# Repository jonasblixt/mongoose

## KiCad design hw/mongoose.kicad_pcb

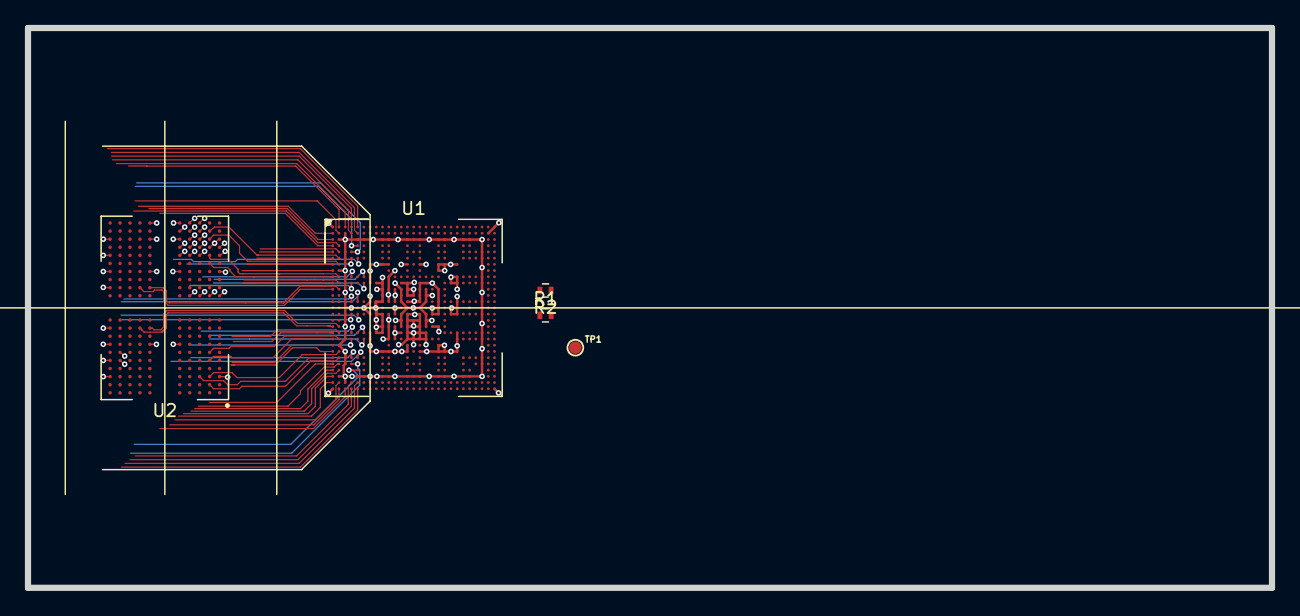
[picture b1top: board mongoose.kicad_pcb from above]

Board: 6 copper layers, 100.0 x 45.0 mm, 5 parts (0 on the bottom side), 80 nets.

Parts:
R1: R0402_240R; R0402
R2: R0402_10k; R0402
TP1: TP; TP_1mm
U1: MIMX8MM6DVTLZAA; BGA-486_27x27_P0.5mm_14.0x14.0mm
U2: MT53B256M32D1NP; BGA-200_12x22_10.0x14.5mm

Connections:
/IMX8MM/DRAM_CA0_A: U1.J6, U2.R2
/IMX8MM/DRAM_CA0_B: U1.W6, U2.H2
/IMX8MM/DRAM_CA1_A: U1.K6, U2.P2
/IMX8MM/DRAM_CA1_B: U1.V6, U2.J2
/IMX8MM/DRAM_CA2_A: U1.E4, U2.R9
/IMX8MM/DRAM_CA2_B: U1.AC4, U2.H9
/IMX8MM/DRAM_CA3_A: U1.D5, U2.R10
/IMX8MM/DRAM_CA3_B: U1.AD5, U2.H10
/IMX8MM/DRAM_CA4_A: U1.N4, U2.R11
/IMX8MM/DRAM_CA4_B: U1.R4, U2.H11
/IMX8MM/DRAM_CA5_A: U1.N5, U2.P11
/IMX8MM/DRAM_CA5_B: U1.R5, U2.J11
/IMX8MM/DRAM_CKE0_A: U1.F4, U2.P4
/IMX8MM/DRAM_CKE0_B: U1.AB4, U2.J4
/IMX8MM/DRAM_CKE1_A: U1.F5, U2.P5
/IMX8MM/DRAM_CKE1_B: U1.AB5, U2.J5
/IMX8MM/DRAM_CK_C_A: U1.L1, U2.P9
/IMX8MM/DRAM_CK_C_B: U1.U1, U2.J9
/IMX8MM/DRAM_CK_T_A: U1.L2, U2.P8
/IMX8MM/DRAM_CK_T_B: U1.U2, U2.J8
/IMX8MM/DRAM_CS0_N_A: U1.K4, U2.R4
/IMX8MM/DRAM_CS0_N_B: U1.W4, U2.H4
/IMX8MM/DRAM_CS1_N_A: U1.J4, U2.R3
/IMX8MM/DRAM_CS1_N_B: U1.V4, U2.H3
/IMX8MM/DRAM_DM0: U1.A4, U2.Y10
/IMX8MM/DRAM_DM1: U1.F1, U2.Y3
/IMX8MM/DRAM_DM2: U1.AB1, U2.C3
/IMX8MM/DRAM_DM3: U1.AG4, U2.C10
/IMX8MM/DRAM_DQ0: U1.A5, U2.AA11
/IMX8MM/DRAM_DQ1: U1.B5, U2.Y11
/IMX8MM/DRAM_DQ2: U1.D2, U2.V11
/IMX8MM/DRAM_DQ3: U1.D1, U2.U11
/IMX8MM/DRAM_DQ4: U1.C1, U2.U9
/IMX8MM/DRAM_DQ5: U1.B1, U2.V9
/IMX8MM/DRAM_DQ6: U1.A3, U2.Y9
/IMX8MM/DRAM_DQ7: U1.B4, U2.AA9
/IMX8MM/DRAM_DQ8: U1.F2, U2.AA2
/IMX8MM/DRAM_DQ9: U1.G2, U2.Y2
/IMX8MM/DRAM_DQ10: U1.J1, U2.U2
/IMX8MM/DRAM_DQ11: U1.J2, U2.V2
/IMX8MM/DRAM_DQ12: U1.K2, U2.U4
/IMX8MM/DRAM_DQ13: U1.K1, U2.V4
/IMX8MM/DRAM_DQ14: U1.E1, U2.Y4
/IMX8MM/DRAM_DQ15: U1.E2, U2.AA4
/IMX8MM/DRAM_DQ16: U1.AB2, U2.B2
/IMX8MM/DRAM_DQ17: U1.AA2, U2.C2
/IMX8MM/DRAM_DQ18: U1.W1, U2.E2
/IMX8MM/DRAM_DQ19: U1.W2, U2.F2
/IMX8MM/DRAM_DQ20: U1.V2, U2.F4
/IMX8MM/DRAM_DQ21: U1.V1, U2.E4
/IMX8MM/DRAM_DQ22: U1.AC1, U2.C4
/IMX8MM/DRAM_DQ23: U1.AC2, U2.B4
/IMX8MM/DRAM_DQ24: U1.AG5, U2.B11
/IMX8MM/DRAM_DQ25: U1.AF5, U2.C11
/IMX8MM/DRAM_DQ26: U1.AD2, U2.E11
/IMX8MM/DRAM_DQ27: U1.AD1, U2.F11
/IMX8MM/DRAM_DQ28: U1.AE1, U2.F9
/IMX8MM/DRAM_DQ29: U1.AF1, U2.E9
/IMX8MM/DRAM_DQ30: U1.AG3, U2.C9
/IMX8MM/DRAM_DQ31: U1.AF4, U2.B9
/IMX8MM/DRAM_DQS0_N: U1.B2, U2.V10
/IMX8MM/DRAM_DQS0_P: U1.A2, U2.W10
/IMX8MM/DRAM_DQS1_N: U1.H1, U2.V3
/IMX8MM/DRAM_DQS1_P: U1.G1, U2.W3
/IMX8MM/DRAM_DQS2_N: U1.Y1, U2.D3
/IMX8MM/DRAM_DQS2_P: U1.AA1, U2.E3
/IMX8MM/DRAM_DQS3_N: U1.AF2, U2.E10
/IMX8MM/DRAM_DQS3_P: U1.AG2, U2.D10
/IMX8MM/DRAM_RESET_N: R2.1, U1.R1
/IMX8MM/NVCC_DRAM: U1.K8, U1.K9, U1.L9, U1.M9, U1.N8, U1.N9, U1.P7, U1.R8, U1.R9, U1.T9, U1.U9, U1.V8, U1.V9
/IMX8MM/P1V1_DRAM: U2.A4, U2.A9, U2.AA3, U2.AA5, U2.AA8, U2.AA10, U2.AB4, U2.AB9, U2.B3, U2.B5, U2.B8, U2.B10, U2.D1, U2.D5, U2.D8, U2.D12, U2.F3, U2.F5, U2.F8, U2.F10, U2.H1, U2.H5, U2.H8, U2.H12, U2.K1, U2.K3, U2.K10, U2.K12, U2.N1, U2.N3, U2.N10, U2.N12, U2.R1, U2.R5, U2.R8, U2.R12, U2.U3, U2.U5, U2.U8, U2.U10, U2.W1, U2.W5, U2.W8, U2.W12
/IMX8MM/P1V8: U2.F1, U2.F12, U2.G4, U2.G9, U2.T4, U2.T9, U2.U1, U2.U12
/IMX8MM/VDD_ARM: U1.R13, U1.R15, U1.T13, U1.T14, U1.T15, U1.U13, U1.U15, U1.V13, U1.V15, U1.V16, U1.W13, U1.W14, U1.W15, U1.W16
/IMX8MM/VDD_DRAM: U1.J10, U1.L10, U1.N10, U1.R10, U1.U10, U1.W10
/IMX8MM/VDD_GPU: U1.P12, U1.R11, U1.U11, U1.V12, U1.W11
/IMX8MM/VDD_SOC: U1.K15, U1.K16, U1.L15, U1.L18, U1.M15, U1.N13, U1.N15, U1.N18, U1.R17, U1.R18, U1.U17, U1.U18
/IMX8MM/VDD_VPU: U1.K12, U1.K13, U1.L11, U1.L13, U1.M13, U1.M14, U1.N11
GND: R1.2, R2.2, U1.A1, U1.A27, U1.AA7, U1.AA9, U1.AA10, U1.AA13, U1.AA15, U1.AA18, U1.AA19, U1.AA21, U1.AB3, U1.AB25, U1.AC3, U1.AC25, U1.AE2, U1.AE5, U1.AE6, U1.AE9, U1.AE10, U1.AE13, U1.AE14, U1.AE15, U1.AE18, U1.AE19, U1.AE22, U1.AE23, U1.AF3, U1.AG1, U1.AG27, U1.B3, U1.B26, U1.C2, U1.C5, U1.C6, U1.C9, U1.C10, U1.C13, U1.C14, U1.C15, U1.C18, U1.C19, U1.C22, U1.C23, U1.E3, U1.E25, U1.F3, U1.F25, U1.G7, U1.G9, U1.G10, U1.G13, U1.G15, U1.G18, U1.G19, U1.G21, U1.H2, U1.H18, U1.J3, U1.J7, U1.J21, U1.J25, U1.K3, U1.K7, U1.K20, U1.K21, U1.K25, U1.L12, U1.L16, U1.M12, U1.M16, U1.N3, U1.N7, U1.N12, U1.N16, U1.N21, U1.N25, U1.P3, U1.P13, U1.P15, U1.P21, U1.P25, U1.R3, U1.R7, U1.R12, U1.R16, U1.R20, U1.R21, U1.R25, U1.T12, U1.T16, U1.U12, U1.U16, U1.V3, U1.V7, U1.V21, U1.V25, U1.W3, U1.W7, U1.W21, U1.W25, U1.Y2, U1.Y13, U1.Y18, U2.A3, U2.A10, U2.AB3, U2.AB5, U2.AB8, U2.AB10, U2.C1, U2.C5, U2.C8, U2.C12, U2.D2, U2.D4, U2.D9, U2.D11, U2.E1, U2.E5, U2.E8, U2.E12, U2.G1, U2.G3, U2.G5, U2.G8, U2.G10, U2.G12, U2.J1, U2.J3, U2.J10, U2.J12, U2.K2, U2.K4, U2.K9, U2.K11, U2.N2, U2.N4, U2.N9, U2.N11, U2.P1, U2.P3, U2.P10, U2.P12, U2.T1, U2.T3, U2.T5, U2.T8, U2.T10, U2.T12, U2.V1, U2.V5, U2.V8, U2.V12, U2.W2, U2.W4, U2.W9, U2.W11, U2.Y1, U2.Y5, U2.Y8, U2.Y12
unnamed: R1.1, U1.P2
unnamed: TP1.1, U1.N2

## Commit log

2019-07-31 Initial work
